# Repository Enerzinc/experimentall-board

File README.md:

# Experimental Board

A KiCad 8 hardware project for a general-purpose electronics experimentation / breakout board: a large prototyping platform with indicators, switches, sensors, sound, and power distribution blocks that can be wired up for bench experiments.

Repository: [Enerzinc/experimentall-board](https://github.com/Enerzinc/experimentall-board)

## Repository layout

```
experimental_board/
├── ExperimentalBoard/                 # Original (v1) design — schematic only
│   ├── ExperimentalBoard.kicad_pro
│   ├── ExperimentalBoard.kicad_sch
│   ├── ExperimentalBoard.kicad_pcb     # empty stub (no board layout yet)
│   ├── ExperimentalBoard-backups/      # KiCad auto-backups (.zip)
│   └── new_exp_board/                  # Current revision (v2)
│       ├── new_exp_board.kicad_pro
│       ├── new_exp_board.kicad_sch
│       ├── new_exp_board.kicad_pcb     # board outline + placement
│       └── new_exp_board-backups/      # KiCad auto-backups (.zip)
└── README.md
```

- **`ExperimentalBoard/`** — first iteration. Contains the full schematic (114 symbols) including the power-supply section, but the PCB file is still empty.
- **`ExperimentalBoard/new_exp_board/`** — current iteration. Schematic (93 symbols) plus a laid-out PCB.

## Features

### Power (v1 schematic)
- DC barrel jack input (12 V)
- TBU-CA-025-500 transient-blocking protection and 1N5819 Schottky diodes
- Linear regulators: LM7809 (9 V), LM7805 (5 V), LD1117 (12 V)
- Labeled distribution headers/rails: `12vin`, `9volts`, `5volts`, `3.3volts`
- Indicator LEDs for the supply rails

### I/O and experiment blocks (both revisions)
- 8 × indicator LEDs (D2–D9 with series resistors)
- 8-bit DIP switch (plus a 4-bit DIP switch in v1)
- Tactile push buttons (MEC 5E / 5G family) and 6 × external switch terminals (`PINSW1`–`PINSW6`)
- 4 × LDR07 light-dependent resistors (light sensing)
- Potentiometers: 10 kΩ, 50 kΩ, 100 kΩ, 5 kΩ + a trimmer (`RV`)
- 2 × buzzers driven by BC547 NPN transistors
- Interfacing: 2.54 mm pin headers, 1.00 mm pin headers, 3-pin pot/sensor headers, 8-bit parallel header, and screw terminals for external wiring
- `5V` / `GND` test points

## Board specifications (new_exp_board)

| Item | Value |
|---|---|
| PCB size | ~276.4 × 169.7 mm |
| Layers | 2 (F.Cu, B.Cu) |
| Thickness | 1.6 mm |
| Footprints placed | 77 |
| Track segments | 0 (unrouted) |
| Mounting holes | none |

## Project status

| Stage | v1 (`ExperimentalBoard`) | v2 (`new_exp_board`) |
|---|---|---|
| Schematic | Complete | Complete |
| Board outline | — | Done (276 × 170 mm) |
| Footprint placement | — | Partial / in progress |
| Routing | — | Not started |
| DRC / fab outputs | — | Not started |

The board is currently in the **placement phase** — the outline and most components are positioned, but no traces have been routed and no gerbers have been generated.

## Getting started

1. Install [KiCad 8.0](https://www.kicad.org/) or newer (files use KiCad 8 file formats, `kicad_sch` v20231120 / `kicad_pcb` v20240108).
2. Open the project file:
   - Current revision: `ExperimentalBoard/new_exp_board/new_exp_board.kicad_pro`
   - Original schematic: `ExperimentalBoard/ExperimentalBoard.kicad_pro`
3. Schematic Editor to review/edit the circuit, PCB Editor to continue placement and routing.

All symbols and footprints come from the standard KiCad 8 libraries — no custom libraries are required.

## Backups

Each design has a `-backups/` folder containing timestamped `.zip` archives written by KiCad's auto-backup. These are safe to keep under version control, but large; trim them if repository size becomes an issue.

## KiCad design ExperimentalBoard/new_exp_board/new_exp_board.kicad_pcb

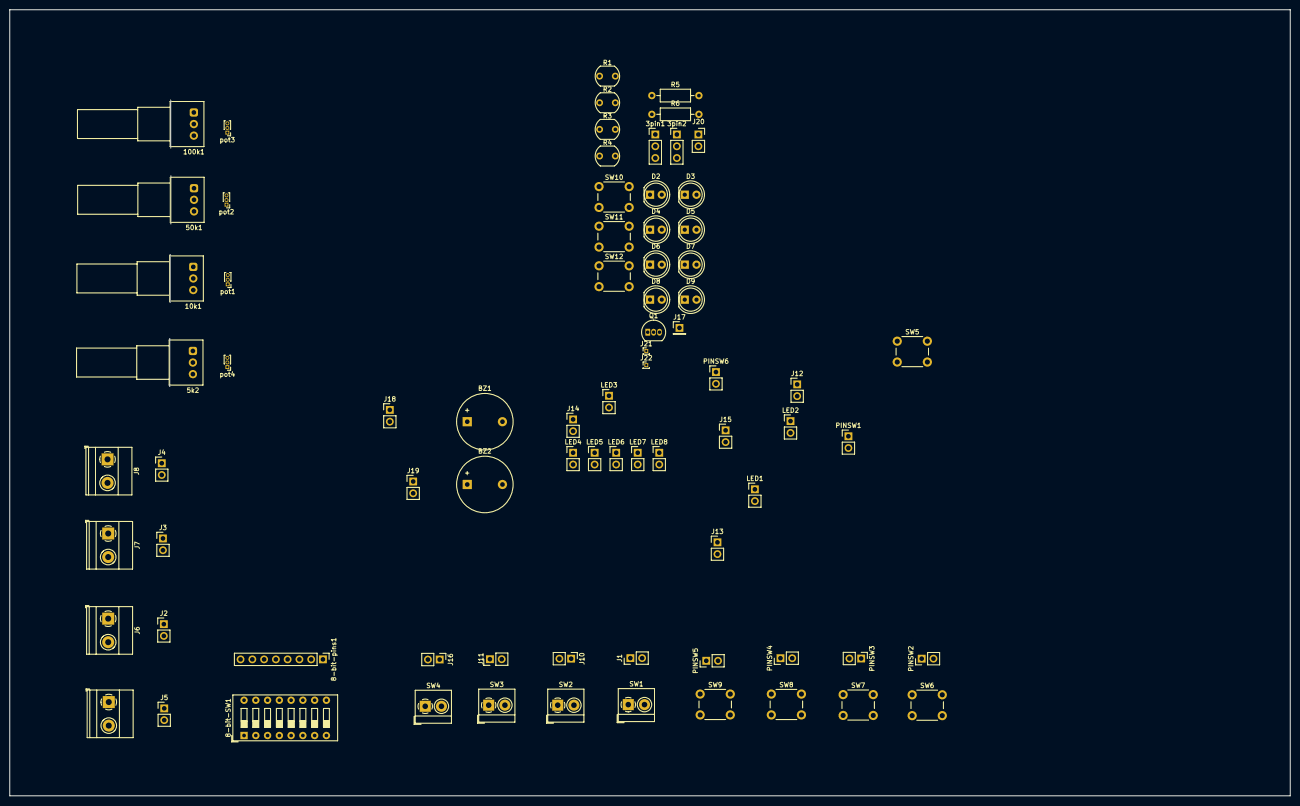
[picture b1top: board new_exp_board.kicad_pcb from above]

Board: 2 copper layers, 276.4 x 169.7 mm, 77 parts (0 on the bottom side), 75 nets, no tracks yet.

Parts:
3pin1, 3pin2: Conn_01x03_Pin; PinHeader_1x03_P2.54mm_Vertical
5k2, 10k1, 50k1, 100k1: R_Potentiometer; Potentiometer_Alps_RK097_Single_Horizontal
8-bit-SW1: SW_DIP_x08; SW_DIP_SPSTx08_Slide_9.78x22.5mm_W7.62mm_P2.54mm
8-bit-pins1: Conn_01x08_Pin; PinHeader_1x08_P2.54mm_Vertical
BZ1, BZ2: Buzzer; Buzzer_12x9.5RM7.6
D2: LED 1; LED_D5.0mm
D3: LED 2; LED_D5.0mm
D4: LED 3; LED_D5.0mm
D5: LED 4; LED_D5.0mm
D6: LED 5; LED_D5.0mm
D7: LED 6; LED_D5.0mm
D8: LED 7; LED_D5.0mm
D9: LED 8; LED_D5.0mm
J1, J2, J3, J4, J5, J10, J11, J12, J13, J14, J15, J16, J18, J19: Conn_01x02_Pin; PinHeader_1x02_P2.54mm_Vertical
J6, J7, J8, J9: Screw_Terminal_01x02; TerminalBlock_Phoenix_MKDS-1,5-2-5.08_1x02_P5.08mm_Horizont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
J17: Conn_01x01_Pin; PinHeader_1x01_P2.54mm_Vertical
J20: Conn_01x02_Socket; PinSocket_1x02_P2.54mm_Vertical
J21: 5V; PinHeader_1x01_P1.00mm_Vertical
J22: GND; PinHeader_1x01_P1.00mm_Vertical
LED1, LED2, LED3, LED4, LED5, LED6, LED7, LED8: Pin_LED 1; PinHeader_1x02_P2.54mm_Vertical
PINSW1, PINSW2, PINSW3, PINSW4, PINSW5, PINSW6: Conn_01x02_Pin; PinHeader_1x02_P2.54mm_Vertical
Q1: BC547; TO-92_Inline
R1, R2, R3, R4: LDR07; R_LDR_5.1x4.3mm_P3.4mm_Vertical
R5, R6: R; R_Axial_DIN0207_L6.3mm_D2.5mm_P10.16mm_Horizontal
SW1, SW2, SW3, SW4: SW_MEC_5G; TerminalBlock_4Ucon_1x02_P3.50mm_Horizontal
SW5, SW6, SW7, SW8, SW9, SW10, SW11, SW12: SW_MEC_5E; SW_PUSH_6mm_H4.3mm
pot1, pot2, pot3, pot4: Conn_01x03_Pin; PinHeader_1x03_P1.00mm_Vertical

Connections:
GND: J22.1, Q1.3 (E)
unnamed: 3pin1.1, SW11.1
unnamed: 3pin1.2, SW11.2
unnamed: 3pin2.1, SW12.1
unnamed: 3pin2.2, SW12.2
unnamed: 8-bit-SW1.9, 8-bit-pins1.1
unnamed: 8-bit-SW1.10, 8-bit-pins1.2
unnamed: 8-bit-SW1.11, 8-bit-pins1.3
unnamed: 8-bit-SW1.12, 8-bit-pins1.4
unnamed: 8-bit-SW1.13, 8-bit-pins1.5
unnamed: 8-bit-SW1.14, 8-bit-pins1.6
unnamed: 8-bit-SW1.15, 8-bit-pins1.7
unnamed: 8-bit-SW1.16, 8-bit-pins1.8
unnamed: BZ1.1 (+), J18.1, J20.2, R5.2
unnamed: BZ1.2 (-), Q1.1 (C)
unnamed: BZ2.1 (+), J19.1
unnamed: BZ2.2 (-), J19.2
unnamed: D2.2 (A), LED1.1
unnamed: D2.1 (K), LED1.2
unnamed: D3.2 (A), LED2.1
unnamed: D3.1 (K), LED2.2
unnamed: D4.2 (A), LED3.1
unnamed: D4.1 (K), LED3.2
unnamed: D5.2 (A), LED4.1
unnamed: D5.1 (K), LED4.2
unnamed: D6.2 (A), LED5.1
unnamed: D6.1 (K), LED5.2
unnamed: D7.2 (A), LED6.1
unnamed: D7.1 (K), LED6.2
unnamed: D8.2 (A), LED7.1
unnamed: D8.1 (K), LED7.2
unnamed: D9.2 (A), LED8.1
unnamed: D9.1 (K), LED8.2
unnamed: J1.1, SW1.1 (A), SW1.2 (A)
unnamed: J2.1, J6.1
unnamed: J2.2, J6.2
unnamed: J3.1, J7.1
unnamed: J3.2, J7.2
unnamed: J4.1, J8.1
unnamed: J4.2, J8.2
unnamed: J5.1, J9.1
unnamed: J5.2, J9.2
unnamed: J10.1, SW2.1 (A), SW2.2 (A)
unnamed: J11.1, SW3.1 (A), SW3.2 (A)
unnamed: J12.1, R1.2
unnamed: J12.2, R1.1
unnamed: J13.1, R2.2
unnamed: J13.2, R2.1
unnamed: J14.1, R3.2
unnamed: J14.2, R3.1
unnamed: J15.1, R4.2
unnamed: J15.2, R4.1
unnamed: J16.1, SW4.1 (A), SW4.2 (A)
unnamed: 8-bit-SW1.1, 8-bit-SW1.2, 8-bit-SW1.3, 8-bit-SW1.4, 8-bit-SW1.5, 8-bit-SW1.6, 8-bit-SW1.7, 8-bit-SW1.8, J17.1
unnamed: J18.2, J20.1, R6.2
unnamed: J21.1, R5.1
unnamed: PINSW1.1, SW5.1
unnamed: PINSW2.1, SW6.1
unnamed: PINSW3.1, SW7.1
unnamed: PINSW4.1, SW8.1
unnamed: PINSW5.1, SW9.1
unnamed: PINSW6.1, SW10.1
unnamed: Q1.2 (B), R6.1
unnamed: 10k1.3, pot1.1
unnamed: 10k1.2, pot1.2
unnamed: 10k1.1, pot1.3
unnamed: 50k1.3, pot2.1
unnamed: 50k1.2, pot2.2
unnamed: 50k1.1, pot2.3
unnamed: 100k1.3, pot3.1
unnamed: 100k1.2, pot3.2
unnamed: 100k1.1, pot3.3
unnamed: 5k2.3, pot4.1
unnamed: 5k2.2, pot4.2
unnamed: 5k2.1, pot4.3
